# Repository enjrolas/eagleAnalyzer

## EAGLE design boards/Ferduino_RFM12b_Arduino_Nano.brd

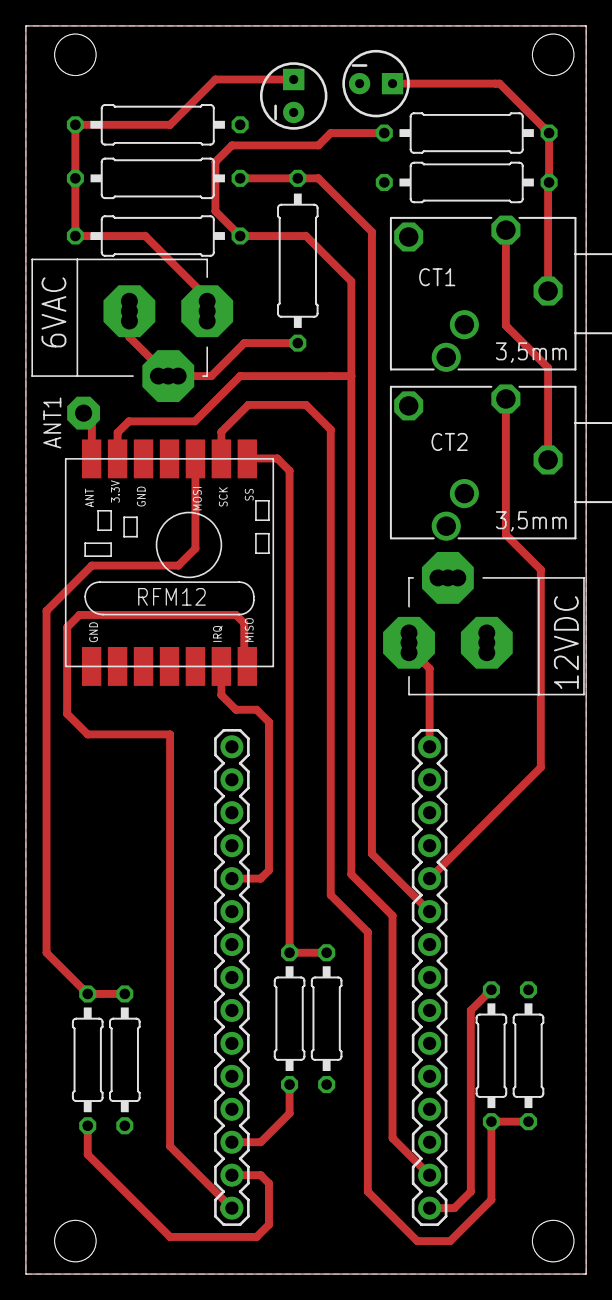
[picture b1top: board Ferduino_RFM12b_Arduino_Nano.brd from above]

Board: 2 copper layers, 43.2 x 96.2 mm, 22 parts (0 on the bottom side), 18 nets.

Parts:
6VAC, 12VDC: POWERSUPPLY_DC21MMX; POWERSUPPLY_DC-21MM
ANT1: RF; PAD-01
C1, C2: 10uF; CPOL-RADIAL-10UF-25V
CT1, CT2: PG203J
JP1, JP2: M15; 1X15
R1, R2, R4, R5, R6: 10k; 0309/12
R3: 100k; 0309/12
R7, R10, R12: 10k; 0207/10
R8, R9, R11: 4k7; 0207/10
U$1: RFM12_SMDSMD; RFM12

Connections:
3.3V: JP2.2, R1.2, R6.2, U$1.3.3V
12V: 12VDC.2, JP2.15
A6: JP2.10, R3.2, R4.2
A7: CT2.5, JP2.11
AC1: 6VAC.1, 6VAC.3, R3.1
AC2: 6VAC.2, C2.1, R4.1, R5.2, R6.1
D2/INT: JP1.11, U$1.IRQ
D10/SS: JP1.3, R8.2
D11/MOSI: JP1.2, R11.1
D12/MISO: JP1.1, U$1.MISO
D13/SCK: JP2.1, R9.1
GND: 12VDC.1, 12VDC.3, C1.2, C2.2, JP1.12, JP2.14, R2.1, R5.1, R7.2, R10.2, R12.1, U$1.GND, U$1.GND1
unnamed: CT1.5, CT2.1
unnamed: ANT1.1, U$1.ANT
unnamed: C1.1, CT1.1, R1.1, R2.2
unnamed: R9.2, R10.1, U$1.SCK
unnamed: R11.2, R12.2, U$1.MOSI
unnamed: R7.1, R8.1, U$1.SS

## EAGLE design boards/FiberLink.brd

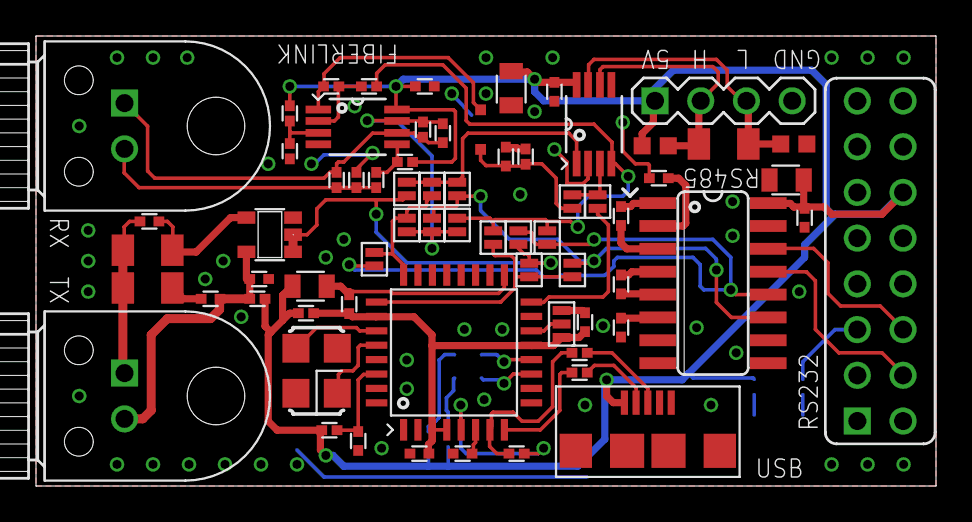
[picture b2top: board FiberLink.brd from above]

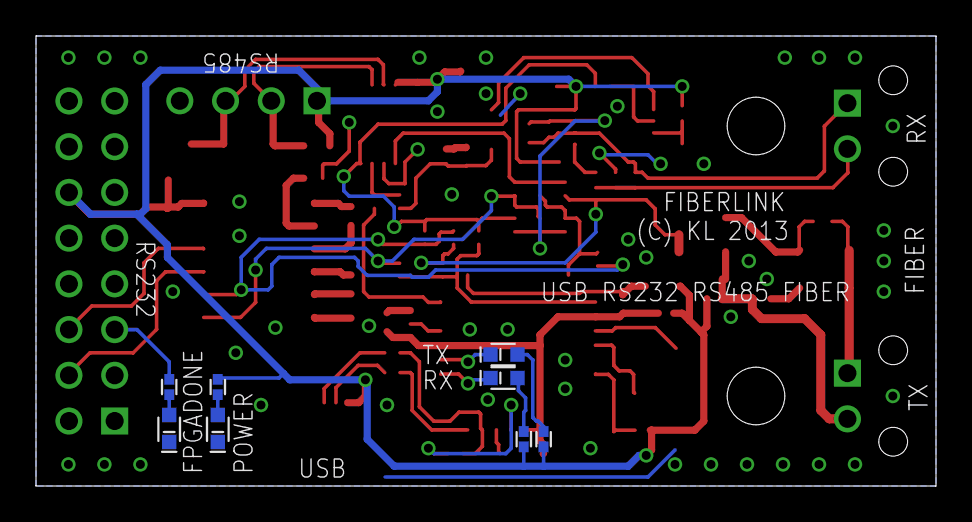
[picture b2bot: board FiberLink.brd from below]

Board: 2 copper layers, 50.0 x 25.0 mm, 77 parts (8 on the bottom side), 50 nets.

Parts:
C1, C2, C3, C4, C5, C6, C7, C8, C9, C10, C11, C12, C13, C14, C15, C16, C17: C0402
C18, C19, C20: C0805
D1: SN65HVD3088EDMSOP; SOP65P490X110-8N
D2: MAX3232CSE; SO16
D3: 74LVC1G08DBV; SOT23-5
D4: FT232BL; LQFP32
DRILEGEND: DRILEGEND
G1: XTAL_3225_SMD; X_3225
H1: IFE91A; IFO-IFX
H2, H3, H4, H5: CHIP-LED0603
L1, L2: R0402_VISHAY
N1: MAX412CPAMSOP; SOP65P490X110-8N
R1, R2, R3, R4, R5, R8, R9, R10, R11, R12, R13, R14, R15, R16, R19, R28, R29, R30: R0402_VISHAY
R6, R7, R25: R1206
R26, R27: R0603
SJ2: 2; SJ-SMALL
SJ3: 3; SJ-SMALL
SJ4: 4; SJ-SMALL
SJ5: 5; SJ-SMALL
SJ6: 6; SJ-SMALL
SJ7: 7; SJ-SMALL
SJ8: 8; SJ-SMALL
SJ9: 9; SJ-SMALL
SJ10: 10; SJ-SMALL
SJ11: 11; SJ-SMALL
SJ12: 12; SJ-SMALL
SJ13: 13; SJ-SMALL
SJ14: 14; SJ-SMALL
SJ15: 15; SJ-SMALL
SJ17: 17; SJ-SMALL-TRI
V1: IFD91; IFO-IFX
V2: SOD323-R
X1: 629105136821
X2: FE08-2
X3: MA04-1

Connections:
485_HIGH: D1.6, R25.1, R27.2, X3.2
485_LOW: D1.7, R25.2, R26.1, X3.3
+5V: C2.2, C7.1, C15.2, C18.1, C19.1, C20.1, D1.8, D2.16, L1.1, L2.2, N1.8, R2.2, R10.1, R11.2, R12.2, R13.1, R27.1, R28.1, X1.1, X2.12, X3.1
AVCC: C10.1, D4.30, R10.2
CARRIER_SENSE: C16.2, R30.1, SJ14.1, V2.C
FPGADONE: R14.1, X2.5
G1: D4.27, G1.3
GND: C2.1, C5.2, C6.2, C7.2, C8.2, C10.2, C11.2, C12.2, C13.2, C14.2, C15.1, C16.1, C17.2, C18.2, C19.2, C20.2, D1.2, D1.5, D2.15, D3.3, D4.9, D4.17, D4.29, D4.31, H2.C, H5.C, N1.4, R3.1, R6.1, R9.2, R26.2, R30.2, SJ17.2, X1.5, X1.Z1, X1.Z2, X1.Z3, X1.Z4, X2.2, X2.14, X2.16, X3.4
unnamed: C1.1, N1.6, R1.2, R4.2, V1.1
unnamed: N1.1, R8.1, V2.A
unnamed: R1.1, R3.2, R5.1, V1.2
unnamed: D4.12, H3.C
unnamed: N1.5, R2.1, R5.2
unnamed: C4.2, D2.5
unnamed: C4.1, D2.4
unnamed: C3.2, D2.3
unnamed: C3.1, D2.1
unnamed: C6.1, D2.6
unnamed: C5.1, D2.2
unnamed: D2.14, X2.6
unnamed: D2.13, X2.4
unnamed: D4.11, H4.C
unnamed: C9.1, H1.1, R6.2, R7.2
unnamed: N1.3, R9.1, R28.2
unnamed: C9.2, D3.4, R7.1
unnamed: H3.A, R11.1
unnamed: R15.1, X1.2
unnamed: H4.A, R12.1
unnamed: D4.8, R15.2
unnamed: H2.A, R13.2
unnamed: D4.7, R16.2, R19.1
unnamed: R16.1, X1.3
unnamed: H5.A, R14.2
unnamed: D4.14, SJ17.3
unnamed: D4.5, R19.2
unnamed: N1.2, R8.2, R29.1
unnamed: D4.28, G1.1
RXD_232: D2.12, SJ4.2, SJ7.2, SJ12.1
RXD_485: D1.1, SJ8.2, SJ10.2, SJ13.2
RXD_FIBER: C1.2, N1.7, R4.1, SJ2.1, SJ3.1, SJ9.1
RXD_USB: D4.24, SJ3.2, SJ7.1, SJ10.1
TXD_232: D2.11, SJ2.2, SJ6.2, SJ13.1
TXD_485: D1.4, R29.2, SJ9.2, SJ11.2, SJ12.2
TXD_FIBER: D3.1, D3.2, SJ4.1, SJ5.1, SJ8.1
TXD_USB: D4.25, SJ5.2, SJ6.1, SJ11.1
TXEN_485: D1.3, SJ14.2, SJ15.2
TXEN_USB: D4.16, SJ15.1
TX_VCC: C8.1, C17.1, D3.5, H1.2, L2.1
USB3V3: C11.1, D4.6
USBVCC: C12.1, C13.1, C14.1, D4.3, D4.4, D4.13, D4.26, L1.2, SJ17.1

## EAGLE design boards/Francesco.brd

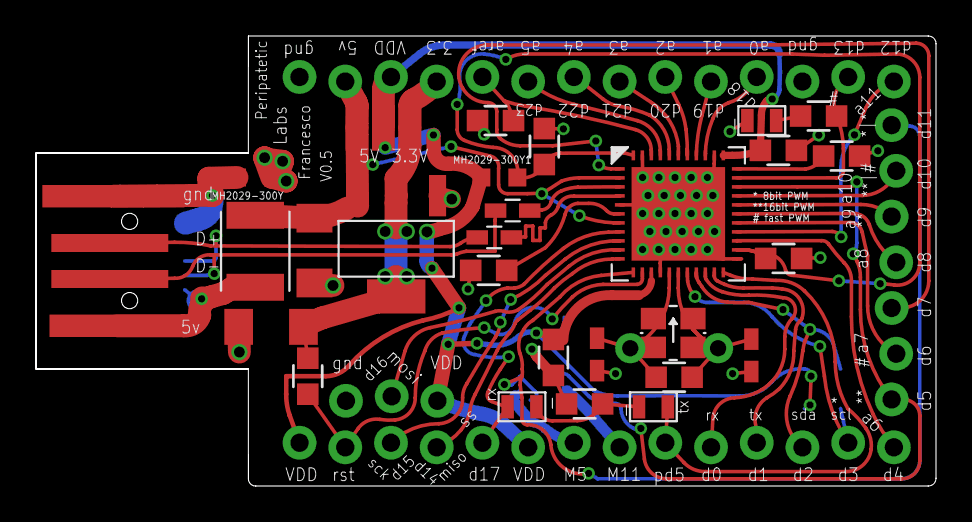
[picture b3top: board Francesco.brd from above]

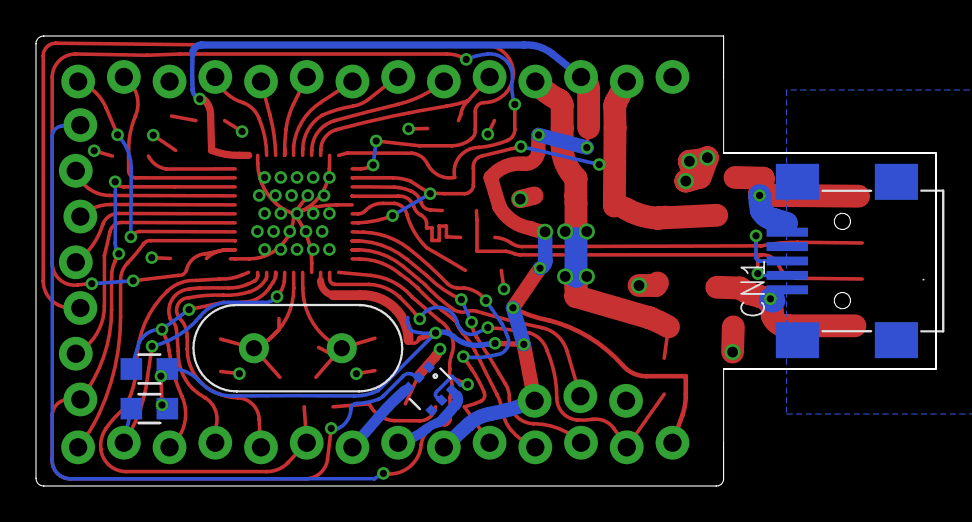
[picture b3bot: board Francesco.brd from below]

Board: 2 copper layers, 50.0 x 25.0 mm, 37 parts (6 on the bottom side), 47 nets.

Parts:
C1, C2: 18pF; 0603-CAP
C3, C9, C10, C11, C12: 0.1uF; 0805
C5: 1uF; 0805
C6, C7: 10uF; 1210
CN1: USB-MINIB
JP1: 1X03_LOCK
JP4: 1X07_LOCK
MH2029-300Y, MH2029-300Y1: FERRITE-2029; 2029
PTH-FUSE: FUSE-PTH_MF-MSMF050; MF-MSMF
R1: 1M; 0805
R2, R3: 22; 0603-RES
R4, R6: 10k; 0805
R5, R7: 1k; 0805
R8, R9: 3.3k; 0805
U$1: ATMEGA32U4; QFN-44
U$2: HC49US
U$3: USB-PCB; USB_PCB
U$4: 5V-LDO-ZLDO1117; ZLDO1117
U$5, U$6: M14; 1X14_LOCK
U$7: BRIDGE-3
U$8: CRYSTAL-3.2X2.5; XTAL3.2X2.5
U$9, U$10, U$11: LED0805; 0805-LED
U$12: N-DUAL-MOSFET; SOT-363

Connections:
3V3: C7.1, R6.2, U$4.2, U$4.4, U$6.11, U$7.1
A0: U$1.36, U$6.4
A1: U$1.37, U$6.5
A2: U$1.38, U$6.6
A3: U$1.39, U$6.7
A4: U$1.40, U$6.8
A5: U$1.41, U$6.9
AREF: C10.2, U$1.42, U$6.10
AVDD: C11.1, C12.2, MH2029-300Y1.P$1, U$1.24, U$1.44
D0: U$1.20, U$5.10
D1: U$1.21, U$5.11
D2: R8.2, U$1.19, U$5.12
D3: R9.1, U$1.18, U$5.13
D4: U$1.25, U$5.14
D5: JP4.7, U$1.31, U$12.2
D6: JP4.6, U$1.27
D7: JP4.5, U$1.1
D8: JP4.4, U$1.28
D9: JP4.3, U$1.29
D10: JP4.2, U$1.30
D11: JP4.1, U$1.12, U$12.5
D12: U$1.26, U$6.1
D13: R5.1, U$1.32, U$6.2
D+: R3.2, U$1.4
D+IN: CN1.D+, R3.1, U$3.D+
D-: R2.2, U$1.3
D-IN: CN1.D-, R2.1, U$3.D-
GND: C1.2, C2.2, C3.2, C5.2, C6.2, C7.2, C9.1, C10.1, C11.2, C12.1, JP1.3, MH2029-300Y.P$1, R4.2, R7.2, U$1.5, U$1.15, U$1.23, U$1.35, U$1.43, U$1.PAD, U$4.1, U$6.3, U$6.14, U$9.-, U$12.1, U$12.4
HWB: R4.1, U$1.33
M5: U$5.7, U$12.6
M11: U$5.8, U$12.3
MISO: U$1.11, U$5.4
MOSI: JP1.2, U$1.10
unnamed: C1.1, R1.1, U$1.16, U$2.1, U$8.1
unnamed: C2.1, R1.2, U$1.17, U$2.2, U$8.3
unnamed: R7.1, U$10.-, U$11.-
unnamed: R5.2, U$9.+
RESET: R6.1, U$1.13, U$5.2
RXLED: U$1.8, U$5.5, U$11.+
SCK: U$1.9, U$5.3
TXLED: U$1.22, U$5.9, U$10.+
UCAP: C5.1, U$1.6
USB5V: C6.1, PTH-FUSE.P$1, U$1.2, U$1.7, U$4.3, U$6.13, U$7.3
USBGND: CN1.GND, MH2029-300Y.P$2, U$3.GND
USBSHROUD: CN1.GND1, CN1.GND2, CN1.GND3, CN1.GND4
USBVIN: CN1.VBUS, PTH-FUSE.P$2, U$3.5V
VDD: C3.1, C9.2, JP1.1, MH2029-300Y1.P$2, R8.1, R9.2, U$1.14, U$1.34, U$5.1, U$5.6, U$6.12, U$7.2

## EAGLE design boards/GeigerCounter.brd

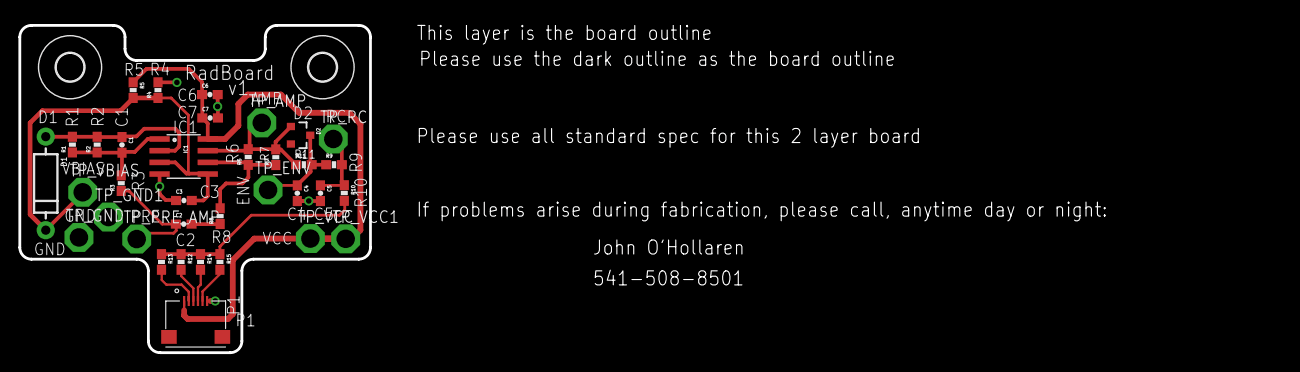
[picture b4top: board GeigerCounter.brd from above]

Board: 2 copper layers, 38.1 x 35.6 mm, 37 parts (0 on the bottom side), 16 nets.

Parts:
C1: 15pF; 0603-CAP
C2: 100p; 0603-CAP
C3: 0.1u; 0603-CAP
C4, C5: DNP; 0603-CAP
C6: 2.2uF; 0603-CAP
C7: 0.1uF; 0603-CAP
D1: S1223; DIODE-1N4001
D2: DNP; SOT23-3
H1, H2: MOUNT-HOLE3.0; 3,0
IC1: OPAMP-DUALU; SO08
P1: XF2M-0615-1A
R1: 10M; 0603-RES
R2, R7: DNP; 0603-RES
R3, R9, R10, R11, R12, R13, R14, R15: 0; 0603-RES
R4, R5: 100; 0603-RES
R6: 100k; 0603-RES
R8: 10k; 0603-RES
TP_AMP: PTR1PAD1-20; P1-20
TP_ENV: PTR1PAD1-20; P1-20
TP_GND, TP_GND1: PTR1PAD1-20; P1-20
TP_PRE_AMP: PTR1PAD1-20; P1-20
TP_RC: PTR1PAD1-20; P1-20
TP_VBIAS: PTR1PAD1-20; P1-20
TP_VCC, TP_VCC1: PTR1PAD1-20; P1-20

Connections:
ENV_DETEC_OUT: C4.1, D2.3, R9.1, R11.2, TP_ENV.TP
GND: C3.1, C4.2, C5.2, C6.2, C7.2, IC1.4, P1.6, R4.2, TP_GND.TP, TP_GND1.TP
IC1A_N: C1.1, D1.A, IC1.2, R1.2, R2.2
IC1A_OUT: C1.2, IC1.1, R1.1, R2.1, R3.2
IC1B_N: IC1.6, R6.1, R7.1, R8.2
IC1B_OUT: D2.1, IC1.7, R6.2, R7.2, R11.1, TP_AMP.TP
INV_AMP_INPUT: C2.2, R8.1
NC1: P1.2, R13.2
NC2: P1.4, R14.2
OUTPUT: R10.2, R12.1, R13.1, R14.1, R15.1
P3.4: P1.5, R15.2
P3.5: P1.3, R12.2
PRE_AMP: C2.1, R3.1, TP_PRE_AMP.TP
RC_OUT: C5.1, R9.2, R10.1, TP_RC.TP
VCC: C6.1, C7.1, IC1.8, P1.1, R5.1, TP_VCC.TP, TP_VCC1.TP
VCC_1.25: C3.2, D1.C, IC1.3, IC1.5, R4.1, R5.2, TP_VBIAS.TP

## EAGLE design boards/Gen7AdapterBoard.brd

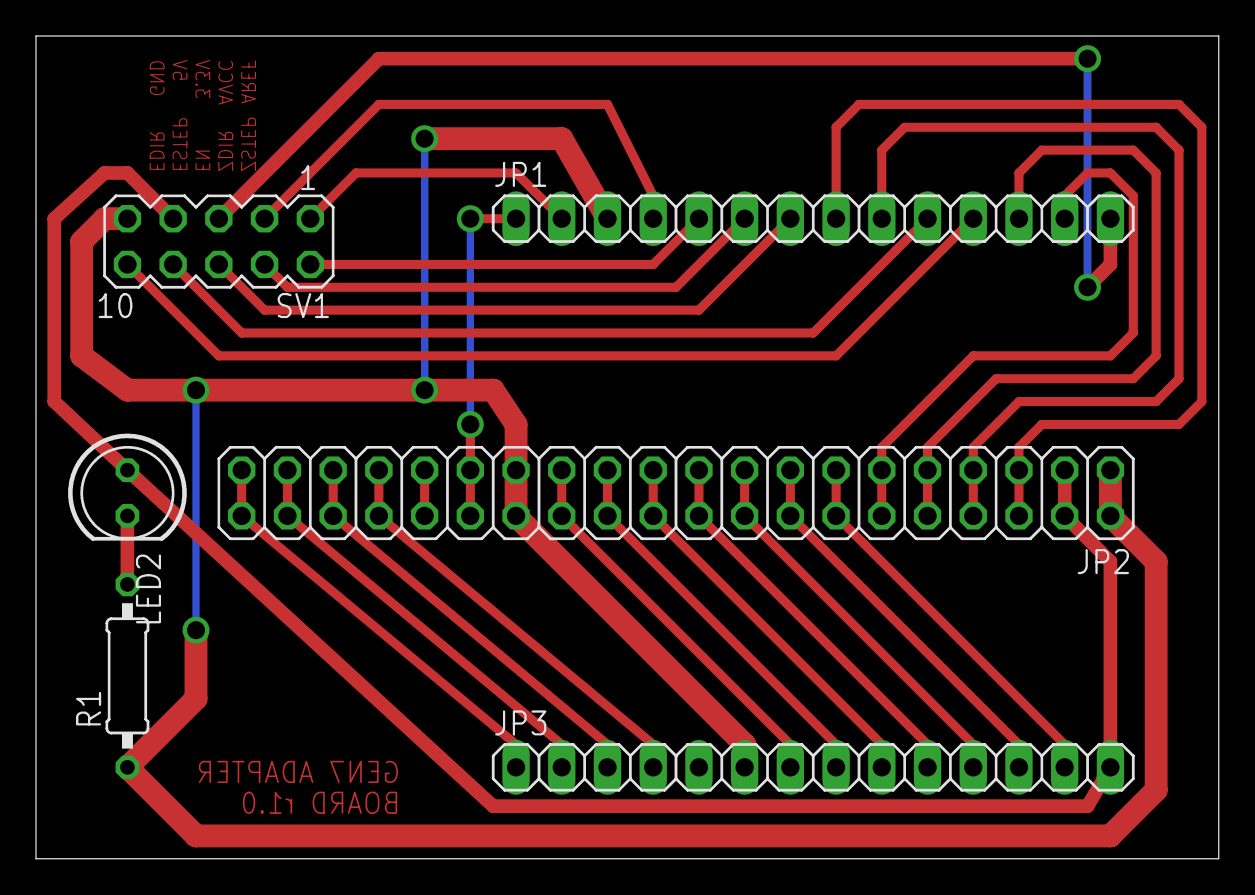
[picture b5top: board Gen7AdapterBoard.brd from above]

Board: 2 copper layers, 65.7 x 45.7 mm, 6 parts (0 on the bottom side), 28 nets.

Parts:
JP1, JP3: 1X14
JP2: 2X20
LED2: LED5MM
R1: 0207/10
SV1: MA05-2

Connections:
+5V: JP2.3, JP2.4, JP3.14, LED2.A, SV1.7
GND: JP1.3, JP2.1, JP2.2, JP2.27, JP2.28, JP3.6, R1.1, SV1.9
unnamed: LED2.K, R1.2
unnamed: JP1.7, SV1.6
unnamed: JP1.14, SV1.5
unnamed: JP1.8, JP2.5, JP2.6
unnamed: JP1.9, JP2.7, JP2.8
unnamed: JP2.13, JP2.14, JP3.13
unnamed: JP2.15, JP2.16, JP3.12
unnamed: JP2.17, JP2.18, JP3.11
unnamed: JP2.19, JP2.20, JP3.10
unnamed: JP2.21, JP2.22, JP3.9
unnamed: JP2.23, JP2.24, JP3.8
unnamed: JP2.25, JP2.26, JP3.7
unnamed: JP1.11, SV1.10
unnamed: JP1.1, JP2.29, JP2.30
unnamed: JP2.31, JP2.32
unnamed: JP2.33, JP2.34, JP3.4
unnamed: JP2.35, JP2.36, JP3.3
unnamed: JP2.37, JP2.38, JP3.2
unnamed: JP2.39, JP2.40, JP3.1
unnamed: JP1.10, SV1.8
unnamed: JP1.6, SV1.4
unnamed: JP1.5, SV1.2
unnamed: JP1.2, SV1.1
unnamed: JP1.4, SV1.3
unnamed: JP1.12, JP2.9, JP2.10
unnamed: JP1.13, JP2.11, JP2.12

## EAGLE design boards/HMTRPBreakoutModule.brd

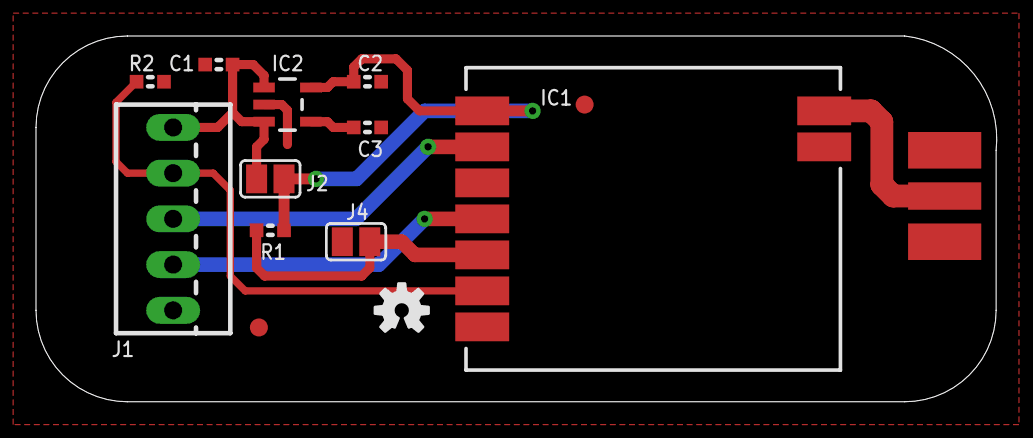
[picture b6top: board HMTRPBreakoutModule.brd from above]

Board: 2 copper layers, 53.4 x 20.3 mm, 14 parts (0 on the bottom side), 9 nets.

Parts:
C1, C2: 2.2µF; 0603
C3: 470pF; 0603
IC1: HM-TRP; HM-TRP-SMD
IC2: MIC5219-3.3YM5; SOT23-5
J1: Interface; 22-23-2051
J2: Regulator Bypass; SJ
J3: Antenna; SMA-EDGE
J4: Config; SJ
JP1, JP2: FIDUCIAL1X2; FIDUCIAL-1X2
R1, R2: 10kΩ; 0603
SY: OSHW-LOGOS; OSHW-LOGO-S

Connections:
+3V3: C2.1, IC1.VCC, IC2.5, J2.2, R1.1
+5V: C1.1, IC2.1, IC2.3, J1.1, J2.1
GND: C1.2, C2.2, C3.1, IC1.AGND, IC1.GND, IC2.2, J1.5, J3.GND@0, J3.GND@1, J3.GND@2, J3.GND@3, J4.1, R2.2
unnamed: IC1.!ENABLE, J1.2, R2.1
unnamed: IC1.DTX, J1.3
unnamed: IC1.ANT, J3.SIG
unnamed: IC1.DRX, J1.4
unnamed: C3.2, IC2.4
unnamed: IC1.!CONFIG, J4.2, R1.2

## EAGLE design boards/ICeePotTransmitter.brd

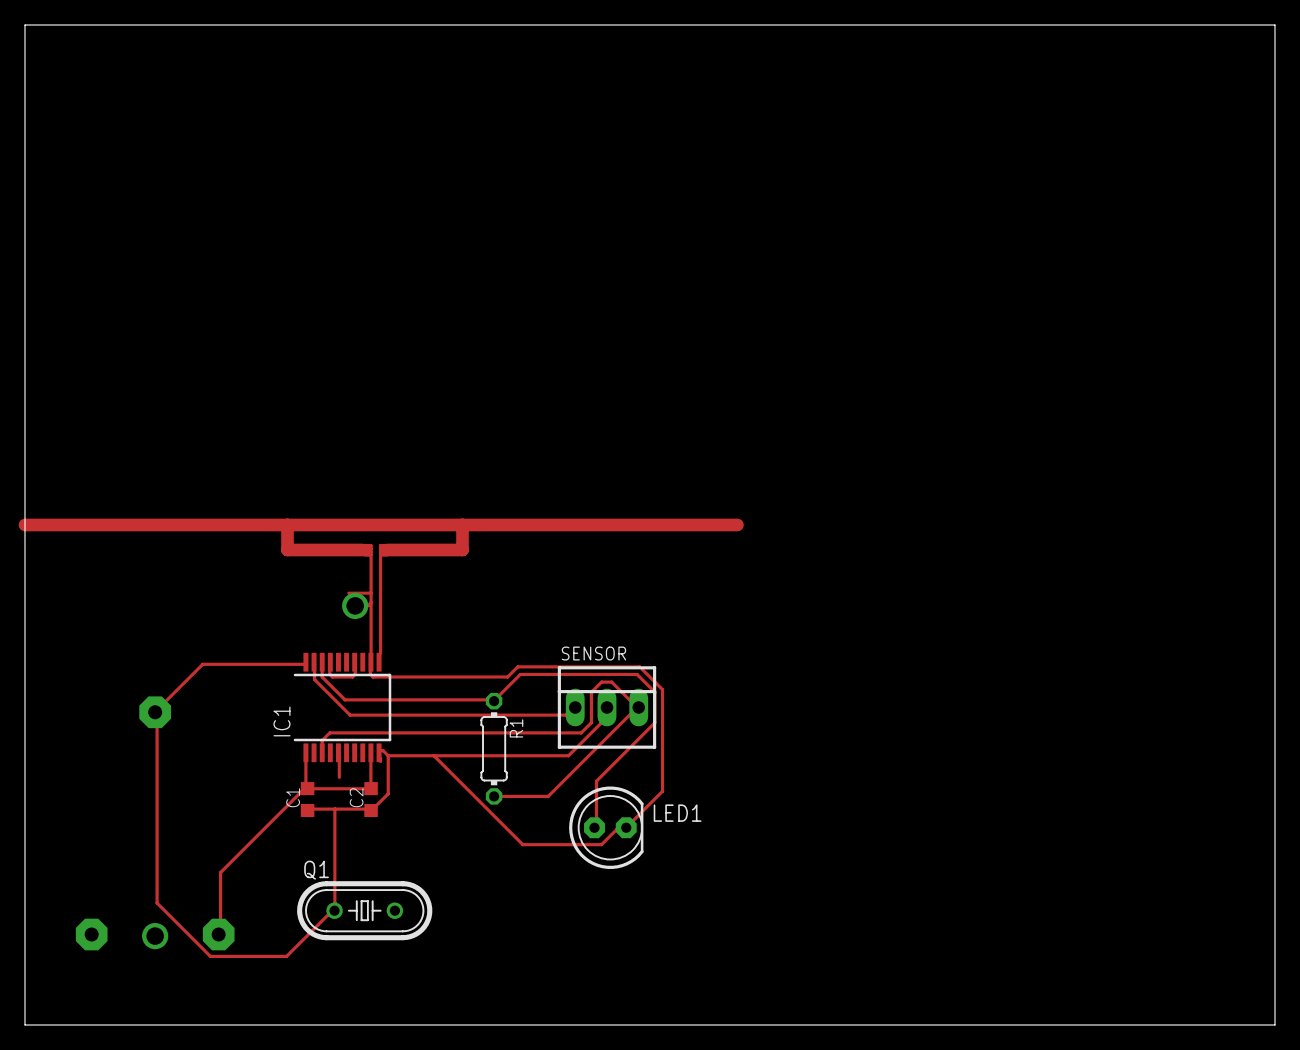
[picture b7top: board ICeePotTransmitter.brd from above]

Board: 2 copper layers, 100.0 x 80.0 mm, 8 parts (1 on the bottom side), 8 nets.

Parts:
C1: 0.1uF; C0603K
C2: 330pF; C0603K
G1: CR2032H
IC1: RFPIC12F675; SOIC20
LED1: LED5MM
Q1: HC49/S
R1: 0204/7
SENSOR: 22-23-2031

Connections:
unnamed: IC1.19, SENSOR.1
unnamed: IC1.14, IC1.17
unnamed: IC1.18, LED1.A, R1.1
unnamed: IC1.3, R1.2, SENSOR.3
unnamed: C1.2, C2.2, G1.+, IC1.1, IC1.9
unnamed: IC1.5, Q1.2
unnamed: C1.1, C2.1, G1.-, IC1.10, IC1.12, IC1.20, LED1.K, Q1.1, SENSOR.2
unnamed: IC1.2, IC1.6

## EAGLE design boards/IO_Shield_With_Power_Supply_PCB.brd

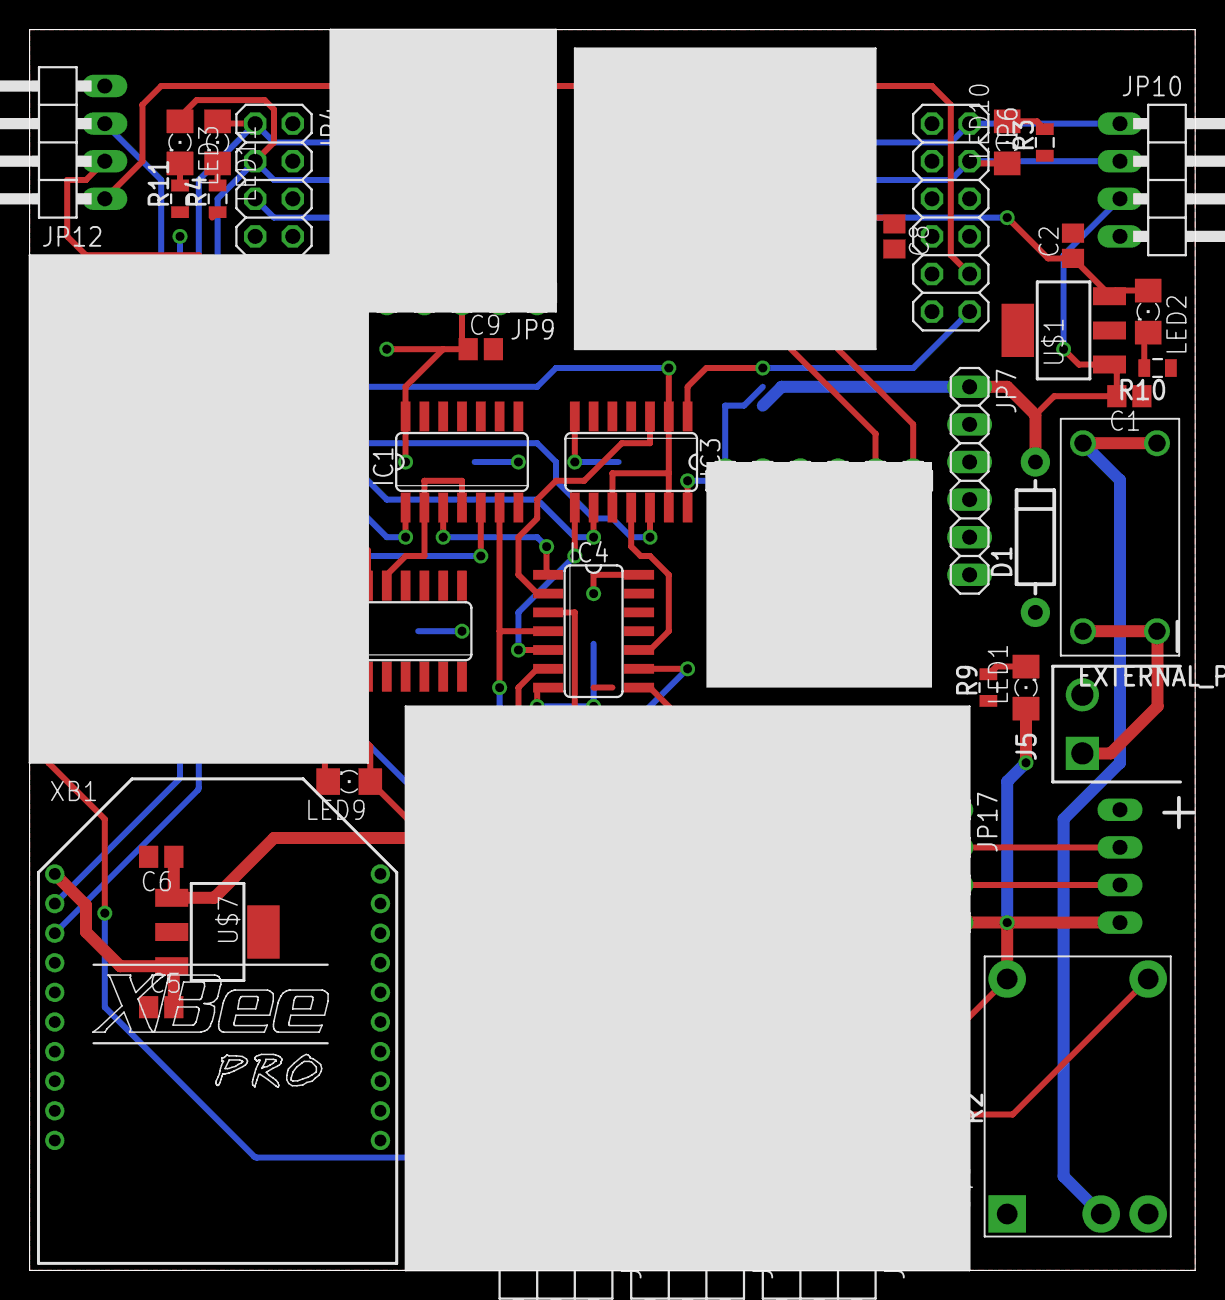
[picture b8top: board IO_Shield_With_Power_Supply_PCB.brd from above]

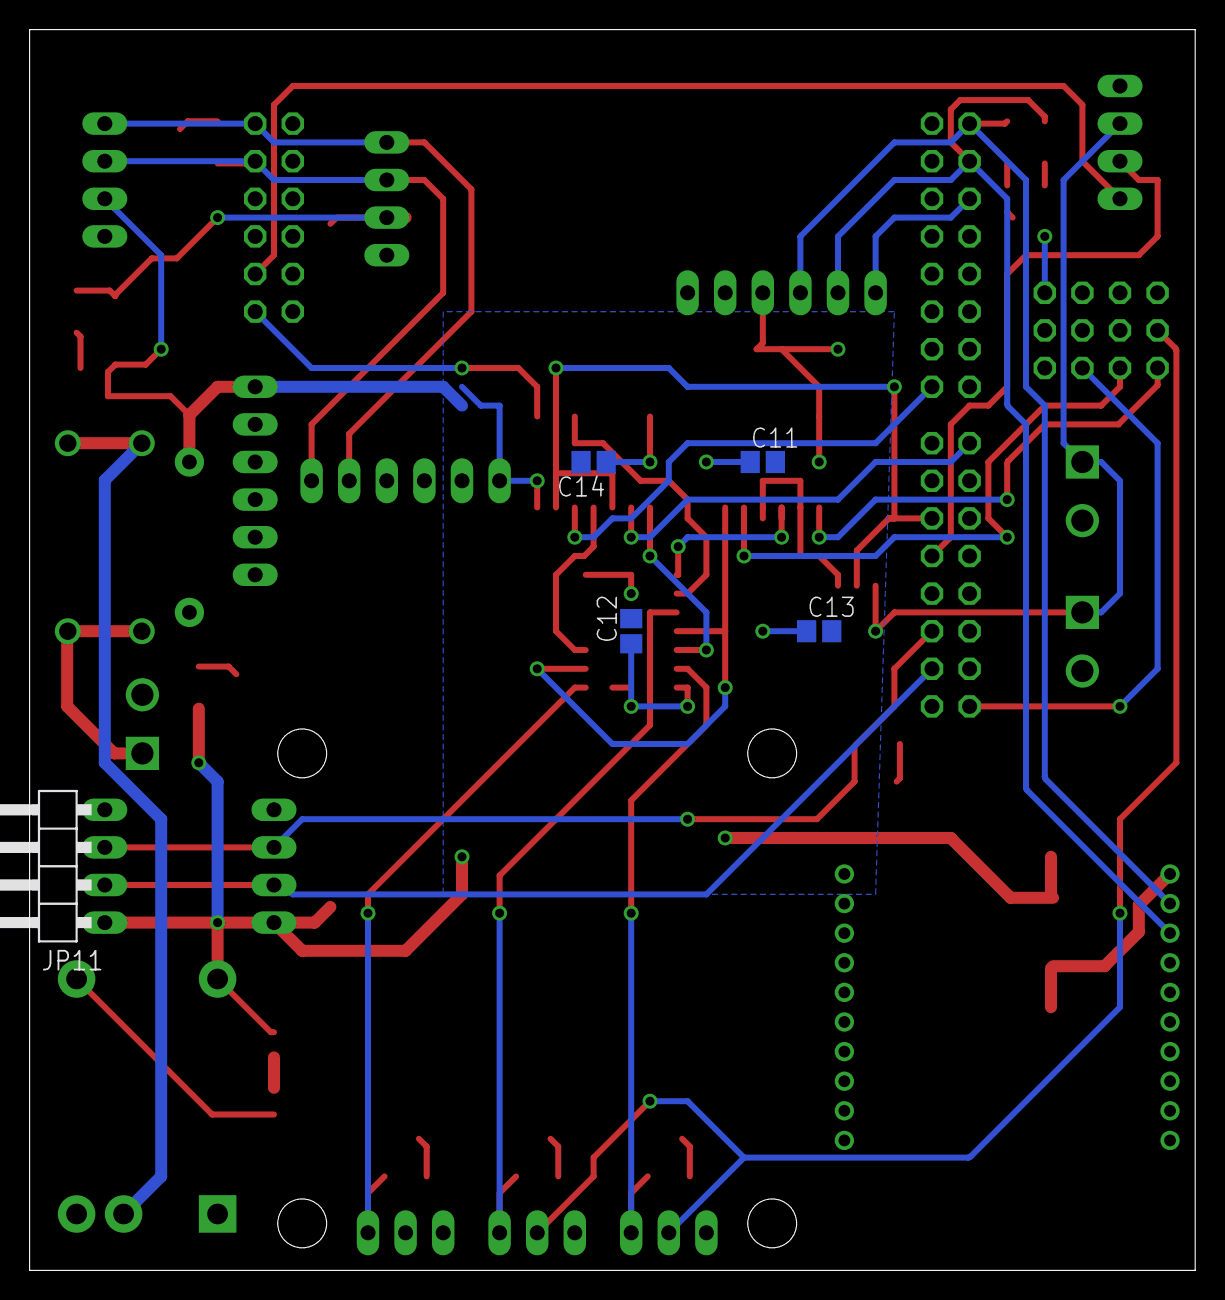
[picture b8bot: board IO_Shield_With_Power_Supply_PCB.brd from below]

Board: 2 copper layers, 78.7 x 83.8 mm, 64 parts (5 on the bottom side), 42 nets.

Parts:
C1, C6: 47uf; C0805
C2, C3, C4, C5, C8, C9, C11, C12, C13, C14: 0.1uf; C0805
D1: DIODE-1N4001
EXTERNAL_POWER: FUSE; FUSE_2AG
IC1, IC3: 74S08D; SO14
IC2: 74LS04D; SO14
IC4: 74LS32D; SO14
J1, J4, J5: POW_CONNECTFEMALE-RA; SOCKET-FEMALE_RA-3.96MM-2
JP1, JP2, JP3: 1X03/90
JP4, JP15: 2X08
JP5, JP17: 1X04
JP6: 2X06
JP7, JP9, JP13: 1X06
JP8: 2X04
JP10, JP11, JP12: 1X04/90
LED1, LED2, LED3, LED5, LED6, LED7, LED9, LED10, LED11: FKIT-LED-1206
R1, R2: 4.7K; 0805
R3, R4, R5, R6, R7, R8, R9, R10, R11: 470; 0805
U$1, U$7: LM3940IMP-3.3; SOT223
U$2, U$3, U$4, U$5: STAND-OFF
U$6: PTN78000
XB1: XBEE-PRO

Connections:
ENABLE: IC2.13, IC3.2, IC3.10, IC3.13, JP15.6, R1.2
GND: C1.1, C2.2, C3.1, C4.1, C5.1, C6.2, C8.2, C9.2, C11.1, C12.1, C13.1, C14.1, D1.A, IC1.7, IC1.9, IC1.10, IC1.12, IC1.13, IC2.1, IC2.3, IC2.5, IC2.7, IC2.9, IC2.11, IC3.4, IC3.5, IC3.7, IC4.7, IC4.12, IC4.13, J1.2, J4.2, J5.2, JP1.3, JP2.3, JP3.3, JP5.1, JP7.2, JP7.3, JP8.1, JP8.3, JP8.5, JP8.7, JP9.1, JP9.2, JP10.4, JP11.4, JP12.4, JP13.5, JP17.1, R1.1, R2.1, R3.1, R4.1, R5.1, R6.1, R7.1, R8.1, R9.1, R10.1, R11.1, U$1.2, U$6.GND, U$7.2, XB1.10
GPS_RX: JP11.3, JP15.12, JP17.2, LED9.A
GPS_TX: JP11.2, JP15.14, JP17.3
L.MOTOR: IC3.9, JP15.1
unnamed: IC1.3, IC4.1
unnamed: IC1.6, IC4.4, IC4.9
unnamed: IC1.2, IC1.4, IC2.12
unnamed: JP6.10, JP12.1
unnamed: IC3.11, IC4.10
unnamed: IC3.8, IC4.5
unnamed: JP12.2, JP15.8
unnamed: IC4.6, JP1.1, LED5.A
unnamed: IC4.3, JP2.1, LED6.A
unnamed: IC4.8, JP3.1, LED7.A
unnamed: JP1.2, JP2.2, JP8.8
unnamed: EXTERNAL_POWER.P$1, EXTERNAL_POWER.P$2, U$6.V_IN
unnamed: JP8.10, JP15.15
unnamed: C5.2, U$7.3, XB1.1
unnamed: LED3.C, R11.2
unnamed: JP4.5, JP9.6
unnamed: LED10.C, R3.2
unnamed: LED11.C, R4.2
unnamed: LED9.C, R5.2
unnamed: LED5.C, R6.2
unnamed: LED6.C, R7.2
unnamed: LED7.C, R8.2
unnamed: LED1.C, R9.2
unnamed: LED2.C, R10.2
unnamed: IC3.3, IC4.2
unnamed: EXTERNAL_POWER.P$3, EXTERNAL_POWER.P$4, J5.1
unnamed: R2.2, U$6.ADJ
R.MOTOR: IC3.12, JP4.16
REC.MOTOR: IC1.5, JP8.11
REC_RUDDER: IC1.1, JP8.12
RUDDER: IC3.1, JP6.12
SCL: JP5.4, JP6.2, JP10.1, JP13.2
SDA: JP5.3, JP6.4, JP10.2, JP13.1, LED10.A
VCC: C1.2, C3.2, C4.2, C6.1, C9.1, C11.2, C12.2, C13.2, C14.2, D1.C, IC1.14, IC2.14, IC3.14, IC4.14, J1.1, J4.1, JP7.1, JP9.3, JP10.3, JP11.1, JP12.3, JP13.6, JP17.4, LED1.A, U$1.1, U$6.V_OUT, U$7.1
VDD: C2.1, C8.1, JP5.2, LED2.A, U$1.3
XBEE_RX: JP4.1, JP9.4, LED11.A, XB1.2
XBEE_TX: JP4.3, JP9.5, LED3.A, XB1.3

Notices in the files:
parts and their libraries:
SparkFun-Passives: Licensing: CC v3.0 Share-Alike You are welcome to use this library for commercial purposes.
